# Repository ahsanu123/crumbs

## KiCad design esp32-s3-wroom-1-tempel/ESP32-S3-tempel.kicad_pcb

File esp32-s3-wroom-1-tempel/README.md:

# Logs 

- 16 Februari 2026, make a prototype board, but not sure why its not able detected in pc. need to recheck schematic and re make the prototype board.

# ESP32 S3 Tempel

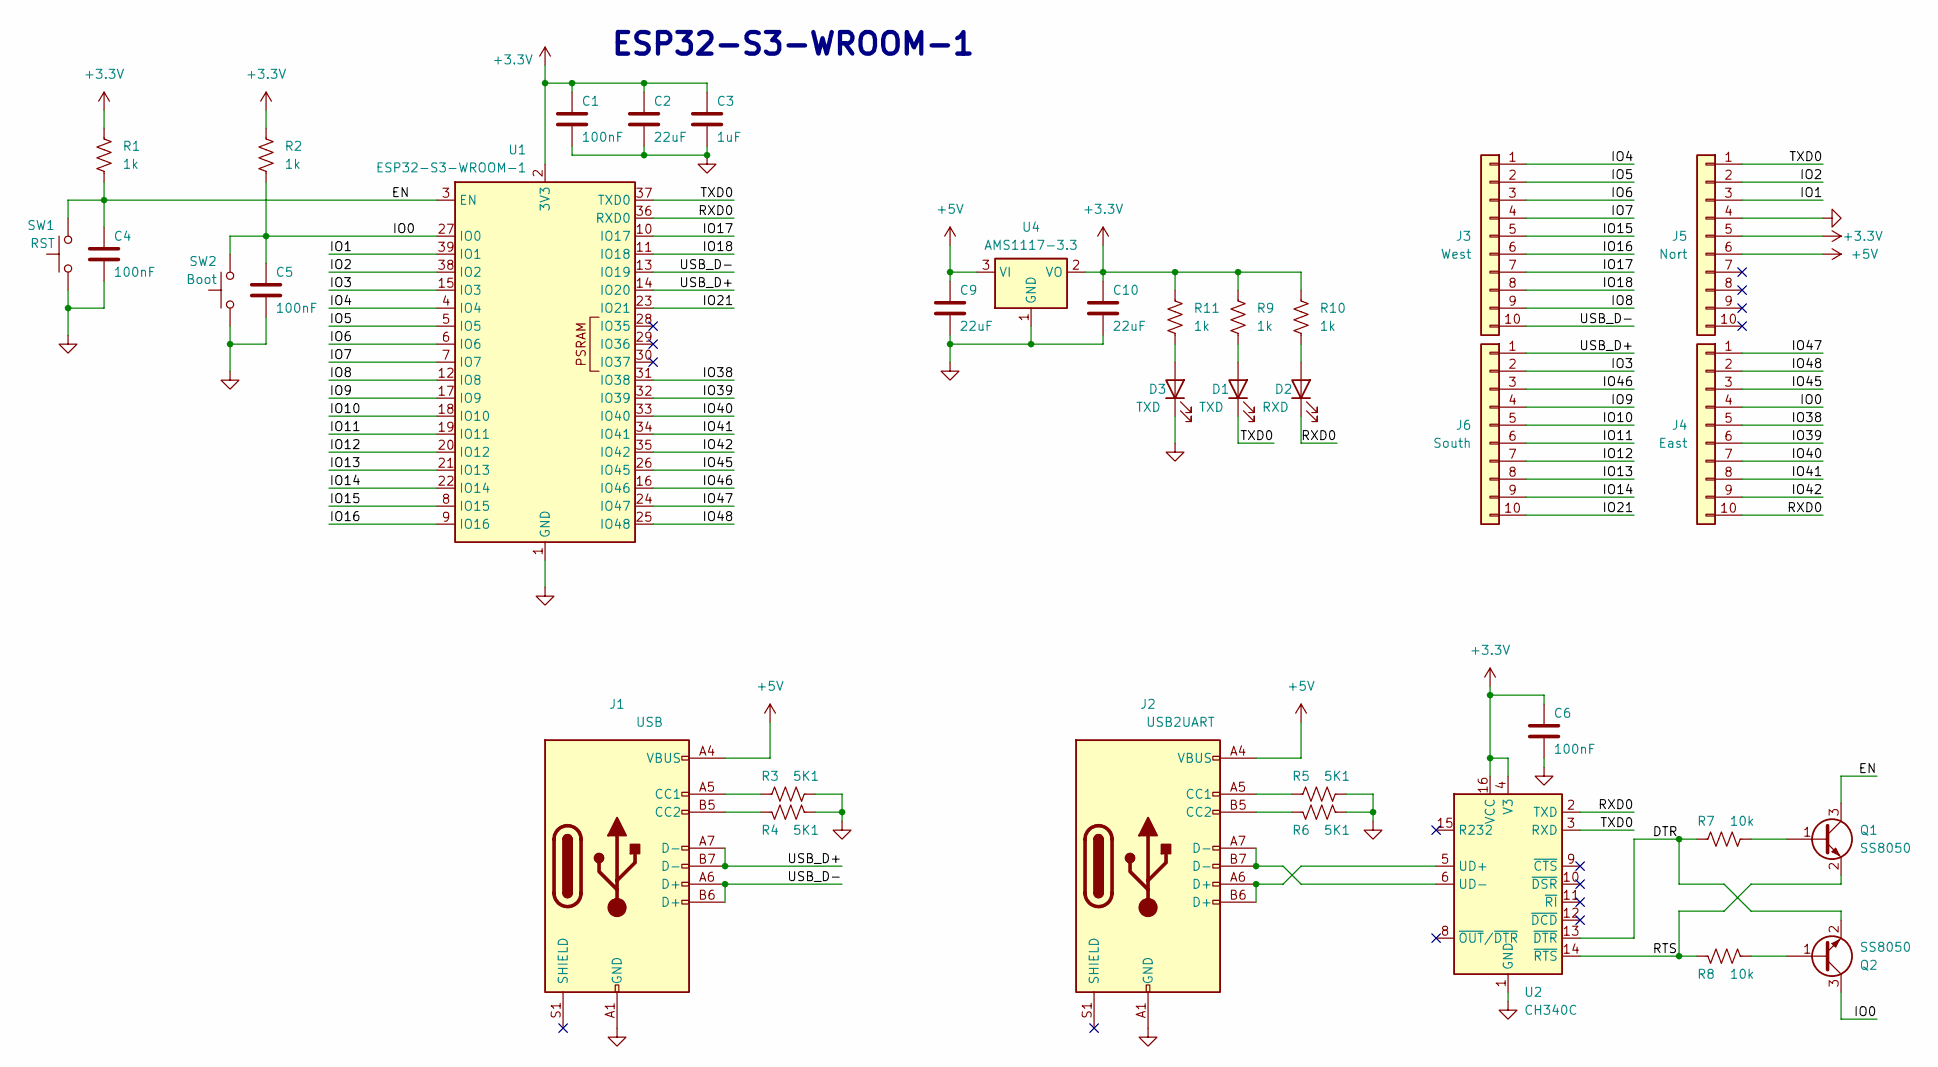
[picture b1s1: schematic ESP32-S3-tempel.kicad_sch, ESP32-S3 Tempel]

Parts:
C1, C4, C5, C6: 100nF; C_0805_2012Metric_Pad1.18x1.45mm_HandSolder
C2, C9, C10: 22uF; C_0805_2012Metric_Pad1.18x1.45mm_HandSolder
C3: 1uF; C_0805_2012Metric_Pad1.18x1.45mm_HandSolder
D1, D3: TXD; LED_1206_3216Metric_Pad1.42x1.75mm_HandSolder
D2: RXD; LED_1206_3216Metric_Pad1.42x1.75mm_HandSolder
J1: USB; USB_C_Receptacle_GCT_USB4110
J2: USB2UART; USB_C_Receptacle_GCT_USB4110
J3: West; PinHeader_1x10_P2.54mm_Vertical
J4: East; PinHeader_1x10_P2.54mm_Vertical
J5: Nort; PinHeader_1x10_P2.54mm_Vertical
J6: South; PinHeader_1x10_P2.54mm_Vertical
Q1, Q2: SS8050; SOT-23_Handsoldering
R1, R2, R9, R10, R11: 1k; R_0805_2012Metric_Pad1.20x1.40mm_HandSolder
R3, R4, R5, R6: 5K1; R_0805_2012Metric_Pad1.20x1.40mm_HandSolder
R7, R8: 10k; R_0805_2012Metric_Pad1.20x1.40mm_HandSolder
SW1: RST; SW_Push_1P1T_NO_6x6mm_H9.5mm
SW2: Boot; SW_Push_1P1T_NO_6x6mm_H9.5mm
U1: ESP32-S3-WROOM-1
U2: CH340C; SOIC-16_3.9x9.9mm_P1.27mm
U4: AMS1117-3.3; SOT-223-3_TabPin2

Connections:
+3.3V: C1.1, C2.1, C3.1, C6.1, C10.1, J5.5, R1.1, R2.1, R9.1, R10.1, R11.1, U1.2 (3V3), U2.4 (V3), U2.16 (VCC), U4.2 (VO)
+5V: C9.1, J1.A4 (VBUS), J1.A9 (VBUS), J1.B4 (VBUS), J1.B9 (VBUS), J2.A4 (VBUS), J2.A9 (VBUS), J2.B4 (VBUS), J2.B9 (VBUS), J5.6, U4.3 (VI)
/DTR: Q2.2 (E), R7.2, U2.13 (~DTR)
/EN: C4.1, Q1.3 (C), R1.2, SW1.2, U1.3 (EN)
/IO0: C5.1, J4.4, Q2.3 (C), R2.2, SW2.2, U1.27 (IO0)
/IO1: J5.3, U1.39 (IO1)
/IO2: J5.2, U1.38 (IO2)
/IO3: J6.2, U1.15 (IO3)
/IO4: J3.1, U1.4 (IO4)
/IO5: J3.2, U1.5 (IO5)
/IO6: J3.3, U1.6 (IO6)
/IO7: J3.4, U1.7 (IO7)
/IO8: J3.9, U1.12 (IO8)
/IO9: J6.4, U1.17 (IO9)
/IO10: J6.5, U1.18 (IO10)
/IO11: J6.6, U1.19 (IO11)
/IO12: J6.7, U1.20 (IO12)
/IO13: J6.8, U1.21 (IO13)
/IO14: J6.9, U1.22 (IO14)
/IO15: J3.5, U1.8 (IO15)
/IO16: J3.6, U1.9 (IO16)
/IO17: J3.7, U1.10 (IO17)
/IO18: J3.8, U1.11 (IO18)
/IO21: J6.10, U1.23 (IO21)
/IO38: J4.5, U1.31 (IO38)
/IO39: J4.6, U1.32 (IO39)
/IO40: J4.7, U1.33 (IO40)
/IO41: J4.8, U1.34 (IO41)
/IO42: J4.9, U1.35 (IO42)
/IO45: J4.3, U1.26 (IO45)
/IO46: J6.3, U1.16 (IO46)
/IO47: J4.1, U1.24 (IO47)
/IO48: J4.2, U1.25 (IO48)
/RTS: Q1.2 (E), R8.2, U2.14 (~RTS)
/RXD0: D2.1 (K), J4.10, U1.36 (RXD0), U2.2 (TXD)
/TXD0: D1.1 (K), J5.1, U1.37 (TXD0), U2.3 (RXD)
/USB_D+: J1.A7 (D-), J1.B7 (D-), J6.1, U1.14 (IO20)
/USB_D-: J1.A6 (D+), J1.B6 (D+), J3.10, U1.13 (IO19)
GND: C1.2, C2.2, C3.2, C4.2, C5.2, C6.2, C9.2, C10.2, D3.1 (K), J1.A1 (GND), J1.A12 (GND), J1.B1 (GND), J1.B12 (GND), J2.A1 (GND), J2.A12 (GND), J2.B1 (GND), J2.B12 (GND), J5.4, R3.1, R4.1, R5.1, R6.1, SW1.1, SW2.1, U1.1 (GND), U1.40 (GND), U1.41 (GND), U2.1 (GND), U4.1 (GND)
unnamed: D1.2 (A), R9.2
unnamed: D2.2 (A), R10.2
unnamed: D3.2 (A), R11.2
unnamed: J1.A5 (CC1), R3.2
unnamed: J1.B5 (CC2), R4.2
unnamed: J2.A5 (CC1), R5.2
unnamed: J2.B5 (CC2), R6.2
unnamed: Q1.1 (B), R7.1
unnamed: Q2.1 (B), R8.1
unnamed: J2.A6 (D+), J2.B6 (D+), U2.5 (UD+)
unnamed: J2.A7 (D-), J2.B7 (D-), U2.6 (UD-)

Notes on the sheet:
ESP32-S3-WROOM-1

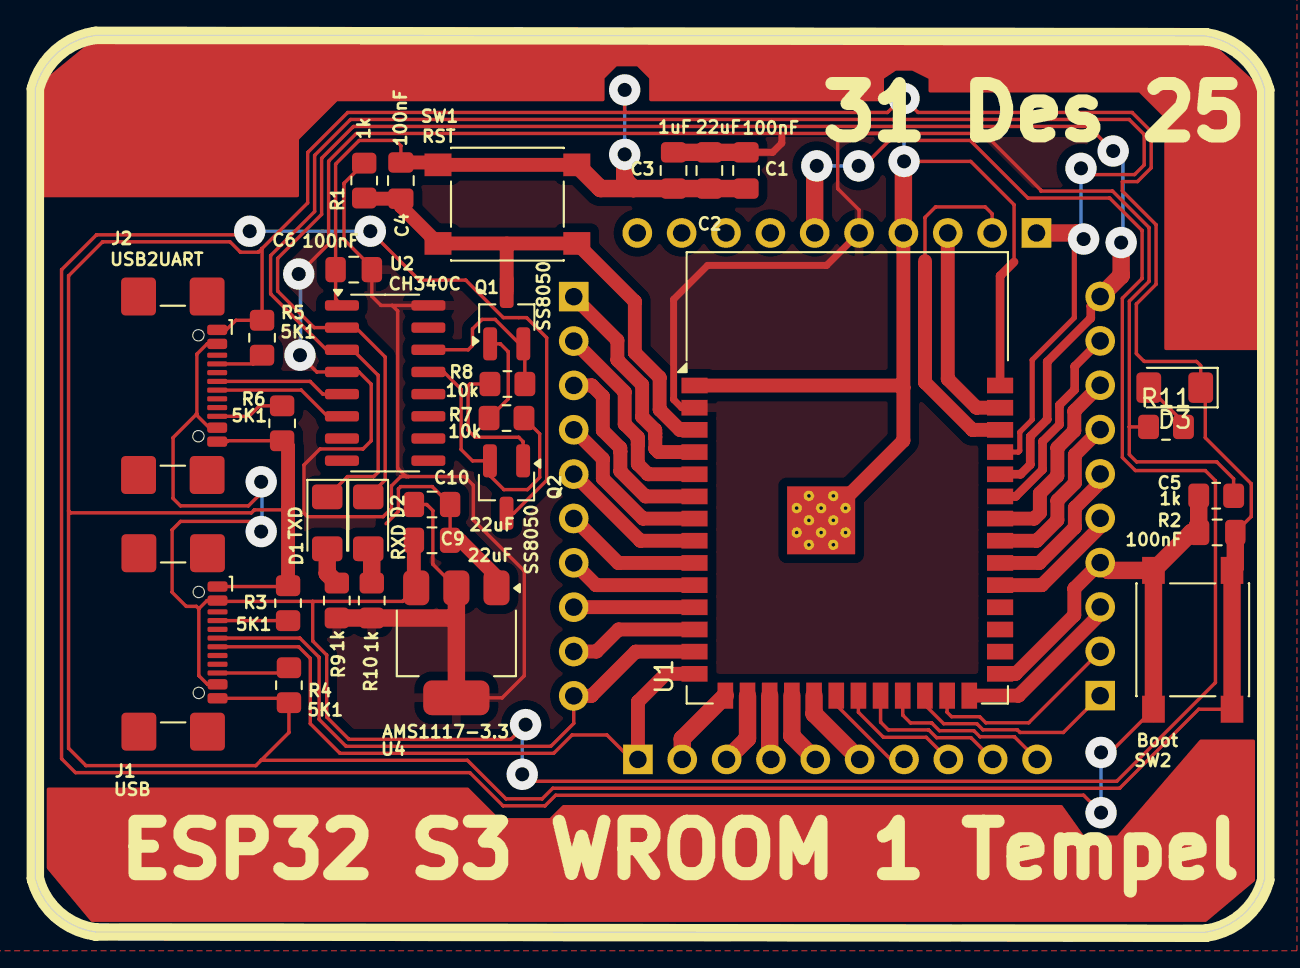
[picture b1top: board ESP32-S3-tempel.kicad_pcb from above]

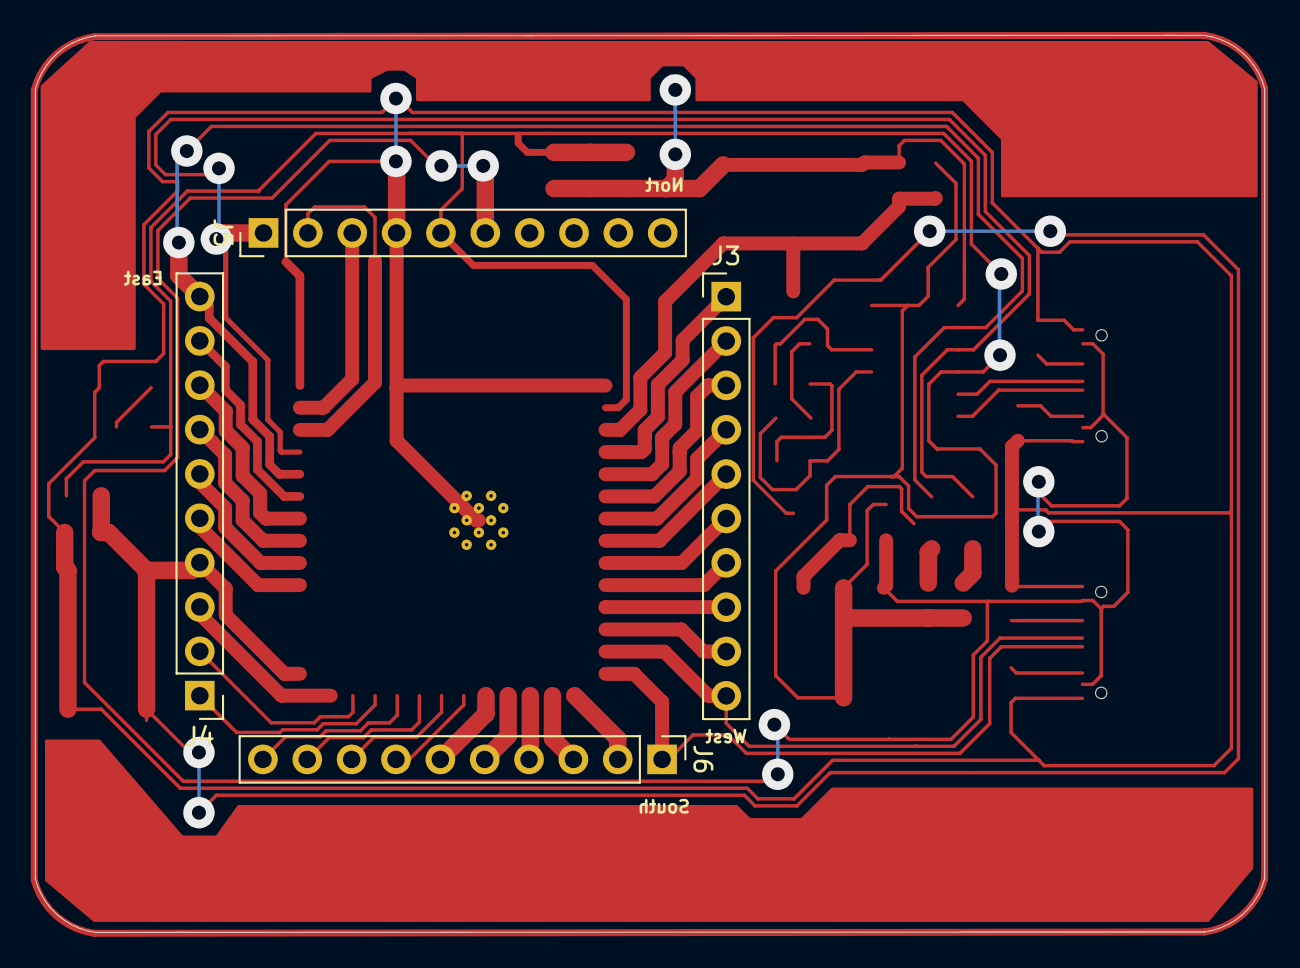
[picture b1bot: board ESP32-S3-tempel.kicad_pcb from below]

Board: 2 copper layers, 70.4 x 51.4 mm, 35 parts (4 on the bottom side), 50 nets.

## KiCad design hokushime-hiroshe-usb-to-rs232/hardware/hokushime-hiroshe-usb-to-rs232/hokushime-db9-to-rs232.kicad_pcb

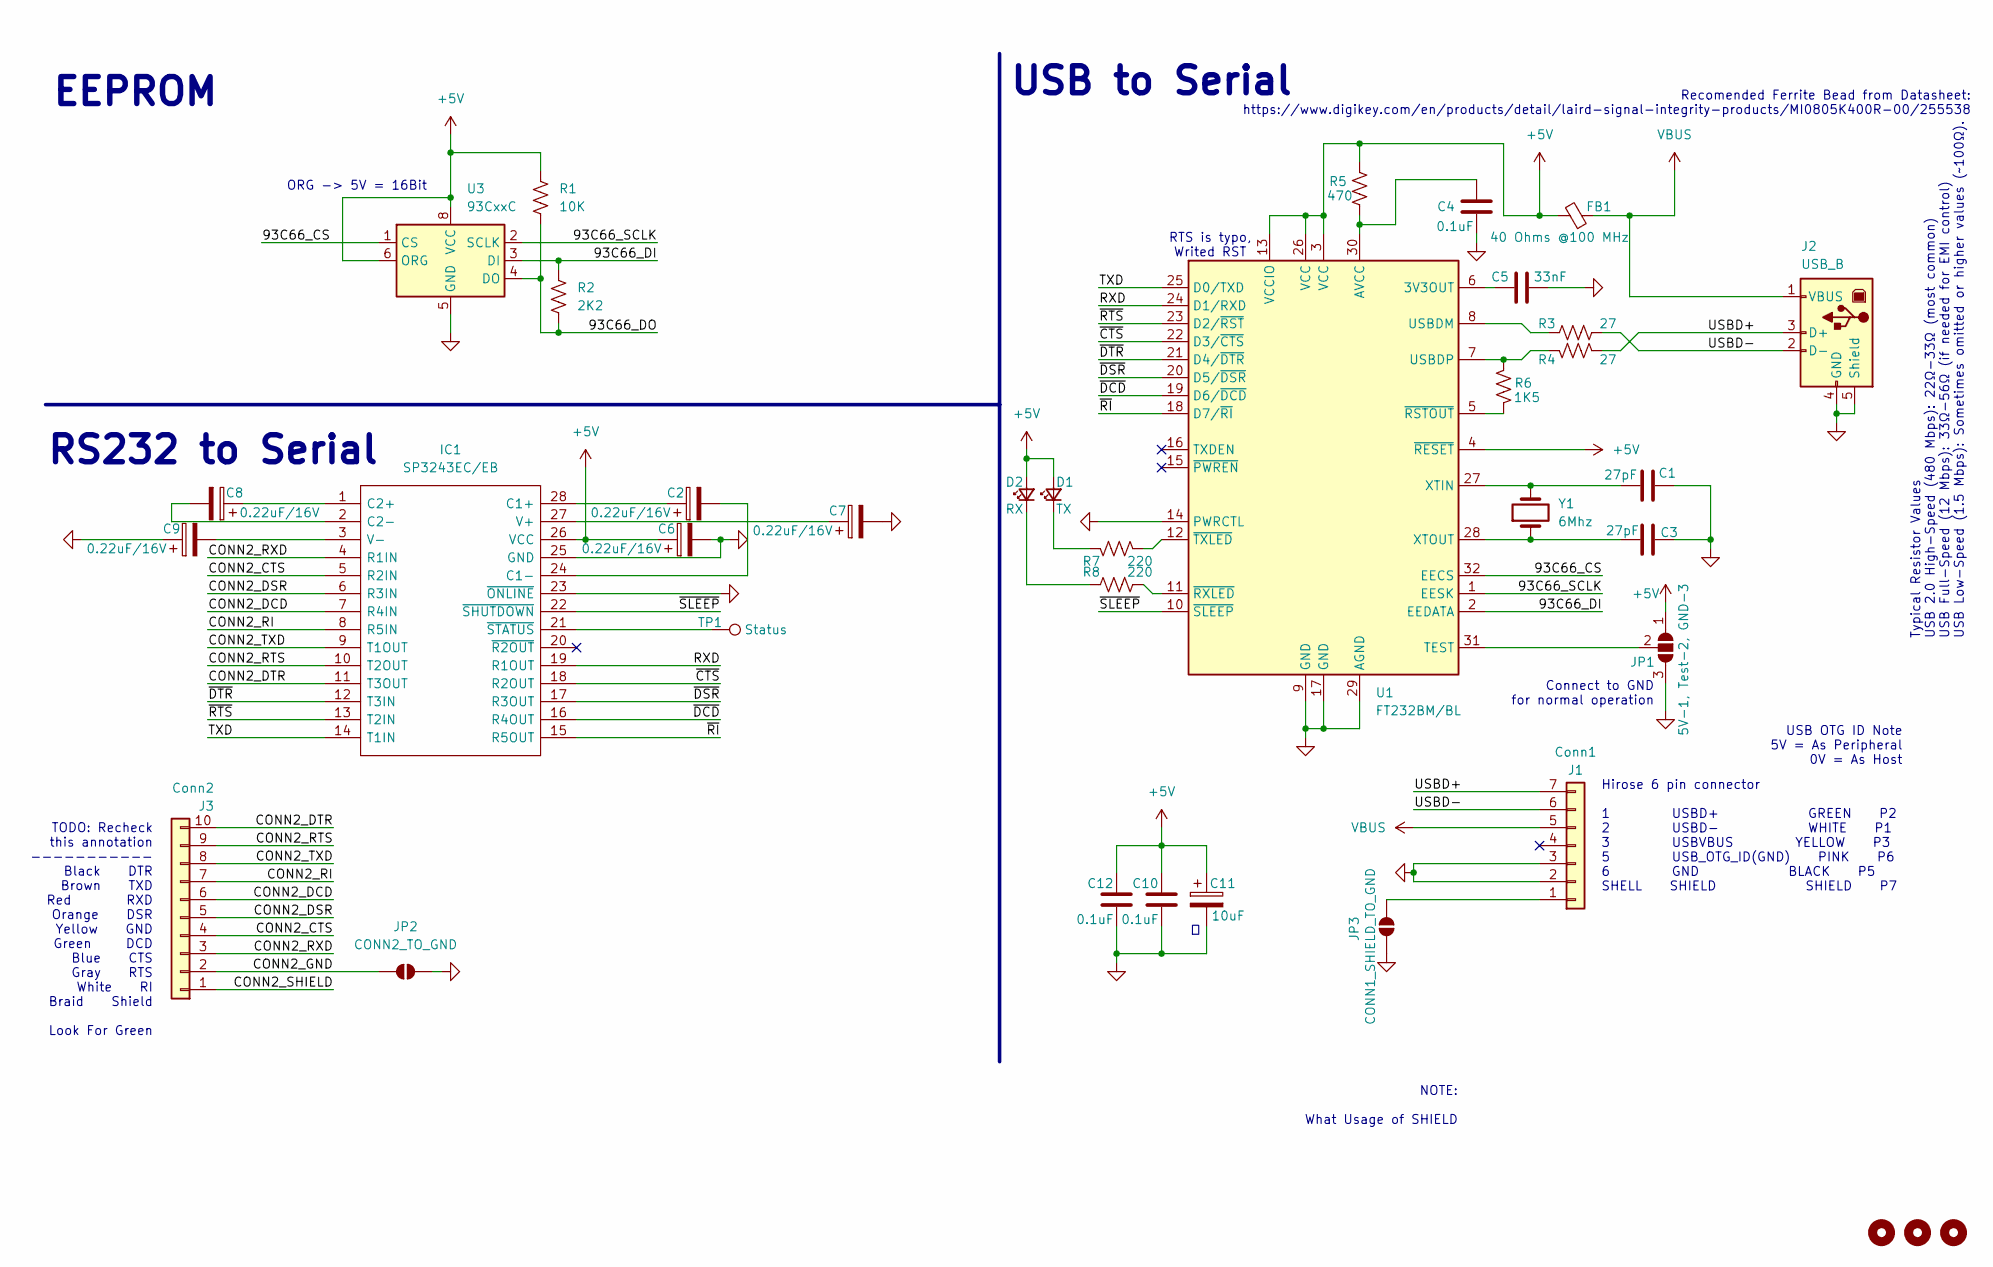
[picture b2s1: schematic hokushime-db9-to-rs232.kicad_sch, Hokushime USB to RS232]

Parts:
C1, C3: 27pF; C_0603_1608Metric_Pad1.08x0.95mm_HandSolder
C2, C6, C7, C8, C9: 0.22uF/16V; C_0603_1608Metric_Pad1.08x0.95mm_HandSolder
C4, C10, C12: 0.1uF; C_0603_1608Metric_Pad1.08x0.95mm_HandSolder
C5: 33nF; C_0603_1608Metric_Pad1.08x0.95mm_HandSolder
C11: 10uF; C_0603_1608Metric_Pad1.08x0.95mm_HandSolder
D1: TX; LED_0805_2012Metric_Pad1.15x1.40mm_HandSolder
D2: RX; LED_0805_2012Metric_Pad1.15x1.40mm_HandSolder
FB1: 40 Ohms @100 MHz; L_0603_1608Metric_Pad1.05x0.95mm_HandSolder
H1, H2, H4: MountingHole; MountingHole_3mm
IC1: SP3243EC/EB; SSOP-28_5.3x10.2mm_P0.65mm; Manufacturer_Part_Number SP3243ECA-L
J1: Conn1; PinHeader_1x07_P2.54mm_Horizontal
J2: USB_B; USB_B_Lumberg_2411_02_Horizontal
J3: Conn2; PinHeader_1x10_P2.54mm_Horizontal
JP1: 5V-1, Test-2, GND-3; SolderJumper-3_P2.0mm_Open_TrianglePad1.0x1.5mm_NumberLabels
JP2: CONN2_TO_GND; SolderJumper-2_P1.3mm_Open_RoundedPad1.0x1.5mm
JP3: CONN1_SHIELD_TO_GND; SolderJumper-2_P1.3mm_Open_RoundedPad1.0x1.5mm
R1: 10K; R_0805_2012Metric_Pad1.20x1.40mm_HandSolder
R2: 2K2; R_0805_2012Metric_Pad1.20x1.40mm_HandSolder
R3, R4: 27; R_0805_2012Metric_Pad1.20x1.40mm_HandSolder
R5: 470; R_0805_2012Metric_Pad1.20x1.40mm_HandSolder
R6: 1K5; R_0805_2012Metric_Pad1.20x1.40mm_HandSolder
R7, R8: 220; R_0805_2012Metric_Pad1.20x1.40mm_HandSolder
TP1: Status; TestPoint_Pad_D1.0mm
U1: FT232BM/BL; LQFP-32_7x7mm_P0.8mm
U3: 93CxxC; SOIC-8_3.9x4.9mm_P1.27mm
Y1: 6Mhz; Crystal_HC49-U_Vertical

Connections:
+5V: C6.1, C10.2, C11.1, C12.2, D1.2 (A), D2.2 (A), FB1.2, IC1.26 (VCC), JP1.1 (A), R1.1, R5.2, U1.3 (VCC), U1.4 (~RESET), U1.13 (VCCIO), U1.26 (VCC), U3.6 (ORG), U3.8 (VCC)
/93C66_CS: U1.32 (EECS), U3.1 (CS)
/93C66_DI: R2.1, U1.2 (EEDATA), U3.3 (DI)
/93C66_DO: R1.2, R2.2, U3.4 (DO)
/93C66_SCLK: U1.1 (EESK), U3.2 (SCLK)
/CONN2_CTS: IC1.5 (R2IN), J3.4
/CONN2_DCD: IC1.7 (R4IN), J3.6
/CONN2_DSR: IC1.6 (R3IN), J3.5
/CONN2_DTR: IC1.11 (T3OUT), J3.10
/CONN2_GND: J3.2, JP2.1 (A)
/CONN2_RI: IC1.8 (R5IN), J3.7
/CONN2_RTS: IC1.10 (T2OUT), J3.9
/CONN2_RXD: IC1.4 (R1IN), J3.3
/CONN2_SHIELD: J3.1
/CONN2_TXD: IC1.9 (T1OUT), J3.8
/RXD: IC1.19 (R1OUT), U1.24 (D1/RXD)
/TXD: IC1.14 (T1IN), U1.25 (D0/TXD)
/USBD+: J1.7, J2.3 (D+), R4.2
/USBD-: J1.6, J2.2 (D-), R3.2
/~CTS: IC1.18 (R2OUT), U1.22 (D3/~CTS)
/~DCD: IC1.16 (R4OUT), U1.19 (D6/~DCD)
/~DSR: IC1.17 (R3OUT), U1.20 (D5/~DSR)
/~DTR: IC1.12 (T3IN), U1.21 (D4/~DTR)
/~RI: IC1.15 (R5OUT), U1.18 (D7/~RI)
/~RTS: IC1.13 (T2IN), U1.23 (D2/~RST)
/~SLEEP: IC1.22 (~SHUTDOWN), U1.10 (~SLEEP)
GND: C1.2, C3.2, C4.1, C5.1, C6.2, C7.2, C9.1, C10.1, C11.2, C12.1, IC1.23 (~ONLINE), IC1.25 (GND), J1.2, J1.3, J2.4 (GND), J2.5 (Shield), JP1.3 (B), JP2.2 (B), JP3.1 (A), U1.9 (GND), U1.14 (PWRCTL), U1.17 (GND), U1.29 (AGND), U3.5 (GND)
unnamed: D1.1 (K), R7.1
unnamed: D2.1 (K), R8.1
unnamed: C2.1, IC1.28 (C1+)
unnamed: C2.2, IC1.24 (C1-)
unnamed: C8.1, IC1.1 (C2+)
unnamed: C8.2, IC1.2 (C2-)
unnamed: C7.1, IC1.27 (V+)
unnamed: C9.2, IC1.3 (V-)
unnamed: IC1.21 (~STATUS), TP1.1
unnamed: J1.1, JP3.2 (B)
unnamed: JP1.2 (C), U1.31 (TEST)
unnamed: C5.2, U1.6 (3V3OUT)
unnamed: C4.2, R5.1, U1.30 (AVCC)
unnamed: R3.1, U1.8 (USBDM)
unnamed: R4.1, R6.2, U1.7 (USBDP)
unnamed: C1.1, U1.27 (XTIN), Y1.2
unnamed: C3.1, U1.28 (XTOUT), Y1.1
unnamed: R6.1, U1.5 (~RSTOUT)
unnamed: R8.2, U1.11 (~RXLED)
unnamed: R7.2, U1.12 (~TXLED)
VBUS: FB1.1, J1.5, J2.1 (VBUS)

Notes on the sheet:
TODO: Recheck this annotation ----------- Black DTR Brown TXD Red RXD Orange DSR Yellow GND Green DCD Blue CTS Gray RTS White RI Braid Shield Look For Green
ORG -> 5V = 16Bit
Recomended Ferrite Bead from Datasheet: https://www.digikey.com/en/products/detail/laird-signal-integrity-products/MI0805K400R-00/255538
RS232 to Serial
USB OTG ID Note 5V = As Peripheral 0V = As Host
RTS is typo, Writed RST
Typical Resistor Values USB 2.0 High-Speed (480 Mbps): 22Ω-33Ω (most common) USB Full-Speed (12 Mbps): 33Ω-56Ω (if needed for EMI control) USB Low-Speed (1.5 Mbps): Sometimes omitted or higher values (~100Ω).
Connect to GND for normal operation
EEPROM
Hirose 6 pin connector 1 USBD+ GREEN P2 2 USBD- WHITE P1 3 USBVBUS YELLOW P3 5 USB_OTG_ID(GND) PINK P6 6 GND BLACK P5 SHELL SHIELD SHIELD P7
NOTE: What Usage of SHIELD
USB to Serial

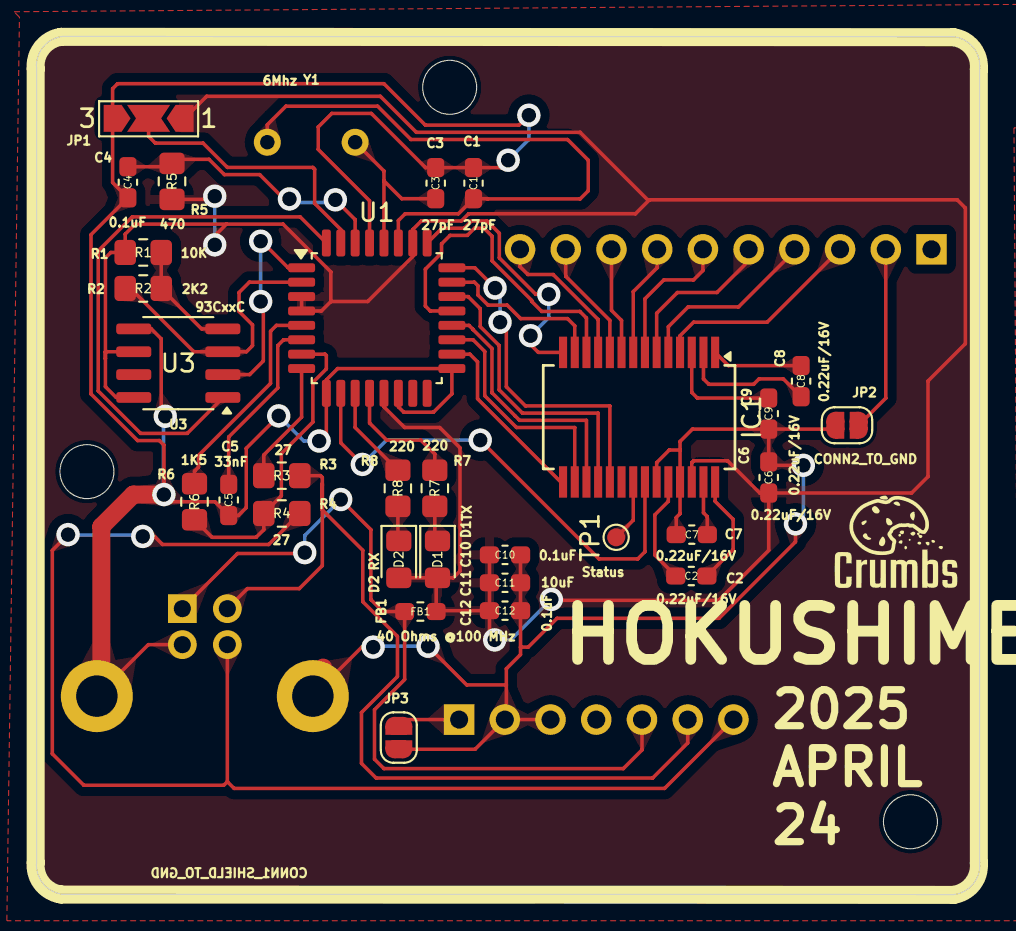
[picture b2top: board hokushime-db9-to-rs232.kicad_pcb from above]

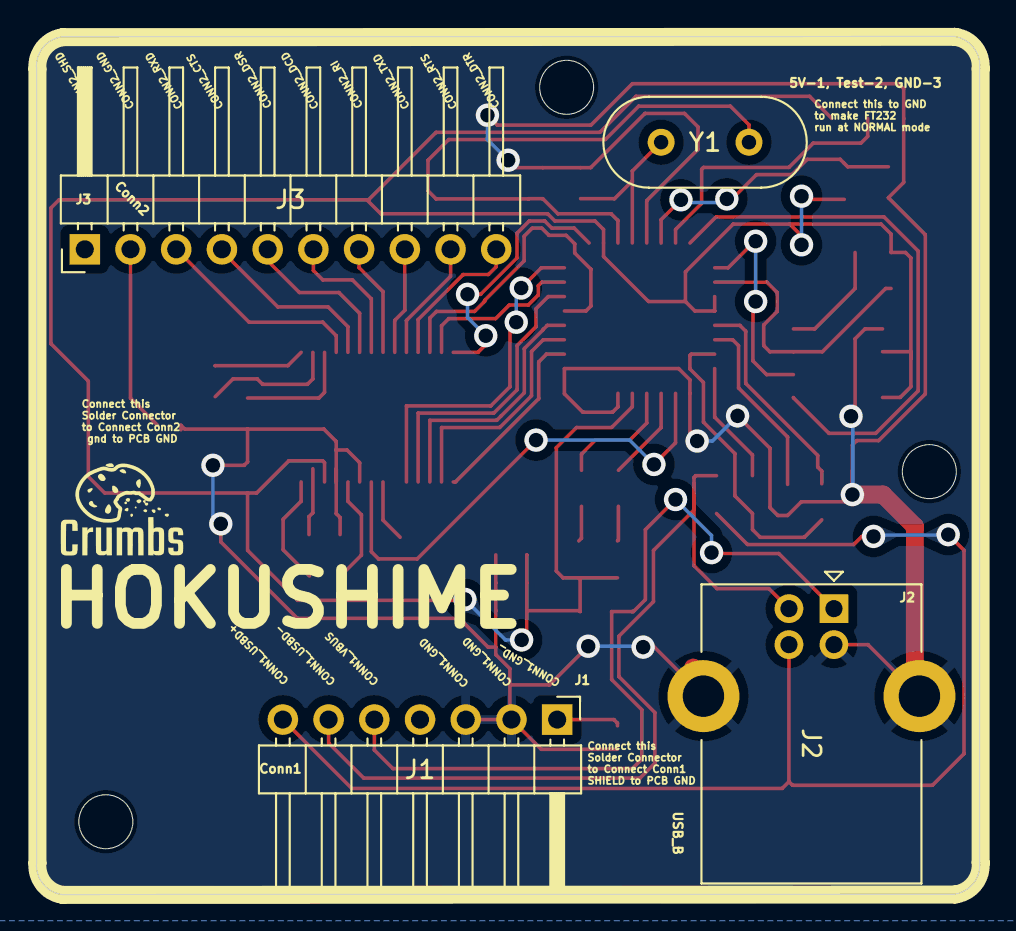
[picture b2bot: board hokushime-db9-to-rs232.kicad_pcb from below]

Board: 2 copper layers, 52.4 x 47.7 mm, 39 parts (5 on the bottom side), 47 nets.

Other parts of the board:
G1, G1#2: LOGO; Crumbs-Logo_Footprint_13x13

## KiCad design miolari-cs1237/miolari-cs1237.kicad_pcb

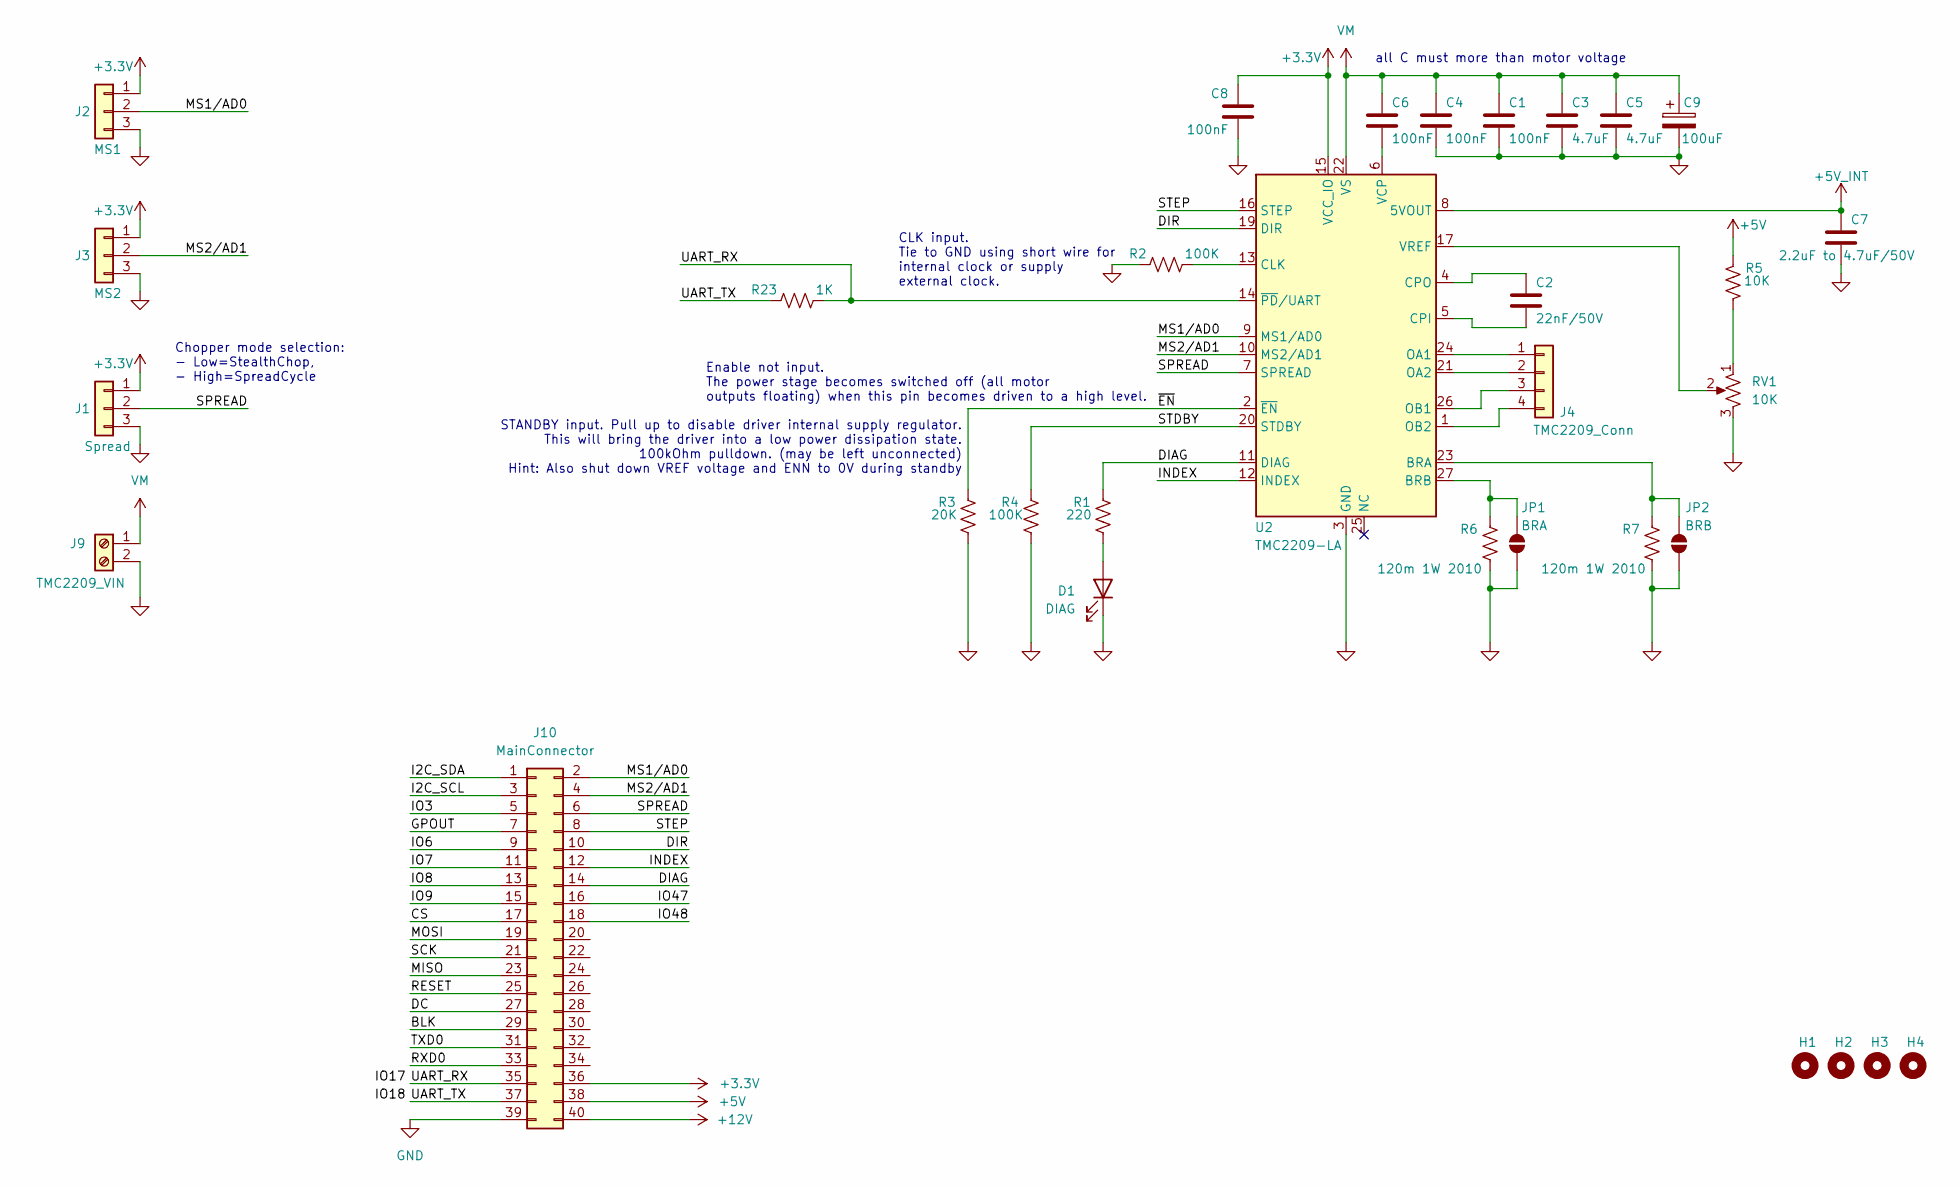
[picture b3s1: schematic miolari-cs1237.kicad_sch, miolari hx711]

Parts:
C1, C4, C6, C8: 100nF; C_0805_2012Metric_Pad1.18x1.45mm_HandSolder
C2: 22nF/50V; C_0805_2012Metric_Pad1.18x1.45mm_HandSolder
C3, C5: 4.7uF; C_0805_2012Metric_Pad1.18x1.45mm_HandSolder
C7: 2.2uF to 4.7uF/50V; C_0805_2012Metric_Pad1.18x1.45mm_HandSolder
C9: 100uF; CP_Radial_D8.0mm_P3.50mm
D1: DIAG; LED_0805_2012Metric_Pad1.15x1.40mm_HandSolder
H1, H2, H3, H4: MountingHole; MountingHole_2mm
J1: Spread; PinHeader_1x03_P2.54mm_Vertical
J2: MS1; PinHeader_1x03_P2.54mm_Vertical
J3: MS2; PinHeader_1x03_P2.54mm_Vertical
J4: TMC2209_Conn; Molex_Nano-Fit_105313-xx04_1x04_P2.50mm_Horizontal
J9: TMC2209_VIN; TerminalBlock_Phoenix_PT-1,5-2-5.0-H_1x02_P5.00mm_Horizontal
J10: MainConnector; IDC-Header_2x20_P2.54mm_Vertical
JP1: BRA; SolderJumper-2_P1.3mm_Open_RoundedPad1.0x1.5mm
JP2: BRB; SolderJumper-2_P1.3mm_Open_RoundedPad1.0x1.5mm
R1: 220; R_0805_2012Metric_Pad1.20x1.40mm_HandSolder
R2, R4: 100K; R_0805_2012Metric_Pad1.20x1.40mm_HandSolder
R3: 20K; R_0805_2012Metric_Pad1.20x1.40mm_HandSolder
R5: 10K; R_0805_2012Metric_Pad1.20x1.40mm_HandSolder
R6, R7: 120m 1W 2010; R_2010_5025Metric
R23: 1K; R_0805_2012Metric_Pad1.20x1.40mm_HandSolder
RV1: 10K; Potentiometer_Bourns_3269W_Vertical
U2: TMC2209-LA; VQFN-28-1EP_5x5mm_P0.5mm_EP3.7x3.7mm

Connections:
+3.3V: C8.1, J1.1, J2.1, J3.1, J10.36, U2.15 (VCC_IO)
+5V: J10.38, R5.1
+5V_INT: C7.1, U2.8 (5VOUT)
+12V: J10.40
/BLK: J10.29
/CS: J10.17
/DC: J10.27
/DIAG: J10.14, R1.1, U2.11 (DIAG)
/DIR: J10.10, U2.19 (DIR)
/GPOUT: J10.7
/I2C_SCL: J10.3
/I2C_SDA: J10.1
/INDEX: J10.12, U2.12 (INDEX)
/IO3: J10.5
/IO6: J10.9
/IO7: J10.11
/IO8: J10.13
/IO9: J10.15
/IO47: J10.16
/IO48: J10.18
/MISO: J10.23
/MOSI: J10.19
/MS1/AD0: J2.2, J10.2, U2.9 (MS1/AD0)
/MS2/AD1: J3.2, J10.4, U2.10 (MS2/AD1)
/RESET: J10.25
/RXD0: J10.33
/SCK: J10.21
/SPREAD: J1.2, J10.6, U2.7 (SPREAD)
/STDBY: R4.1, U2.20 (STDBY)
/STEP: J10.8, U2.16 (STEP)
/TXD0: J10.31
/UART_RX: J10.35, R23.1, U2.14 (~PD/UART)
/UART_TX: J10.37, R23.2
/~EN: R3.1, U2.2 (~EN)
GND: C1.2, C3.2, C4.2, C5.2, C7.2, C8.2, C9.2, D1.1 (K), J1.3, J2.3, J3.3, J9.2, J10.39, JP1.1 (A), JP2.1 (A), R2.2, R3.2, R4.2, R6.2, R7.2, RV1.3, U2.3 (GND), U2.18 (GND), U2.29 (GND)
unnamed: D1.2 (A), R1.2
unnamed: J4.1, U2.24 (OA1)
unnamed: J4.2, U2.21 (OA2)
unnamed: J4.3, U2.26 (OB1)
unnamed: J4.4, U2.1 (OB2)
unnamed: JP1.2 (B), R6.1, U2.27 (BRB)
unnamed: JP2.2 (B), R7.1, U2.23 (BRA)
unnamed: R5.2, RV1.1
unnamed: R2.1, U2.13 (CLK)
unnamed: C2.2, U2.5 (CPI)
unnamed: C2.1, U2.4 (CPO)
unnamed: C6.2, U2.6 (VCP)
unnamed: RV1.2, U2.17 (VREF)
VM: C1.1, C3.1, C4.1, C5.1, C6.1, C9.1, J9.1, U2.22 (VS), U2.28 (VS)

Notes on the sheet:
Chopper mode selection: - Low=StealthChop, - High=SpreadCycle
all C must more than motor voltage
Enable not input. The power stage becomes switched off (all motor outputs floating) when this pin becomes driven to a high level.
STANDBY input. Pull up to disable driver internal supply regulator. This will bring the driver into a low power dissipation state. 100kOhm pulldown. (may be left unconnected) Hint: Also shut down VREF voltage and ENN to 0V during standby
CLK input. Tie to GND using short wire for internal clock or supply external clock.

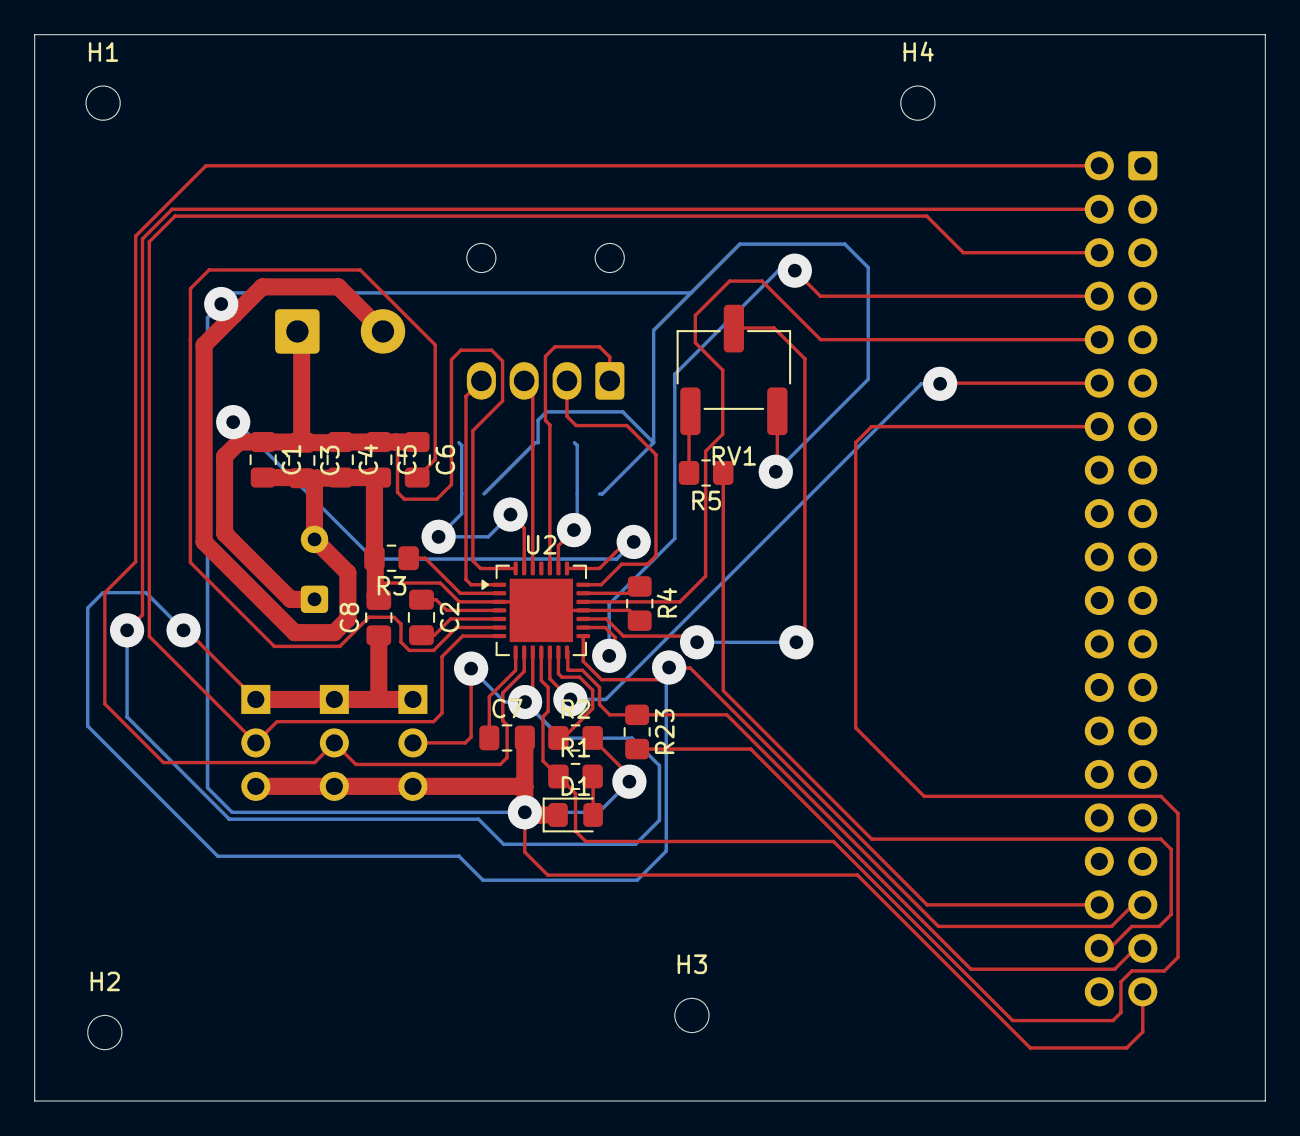
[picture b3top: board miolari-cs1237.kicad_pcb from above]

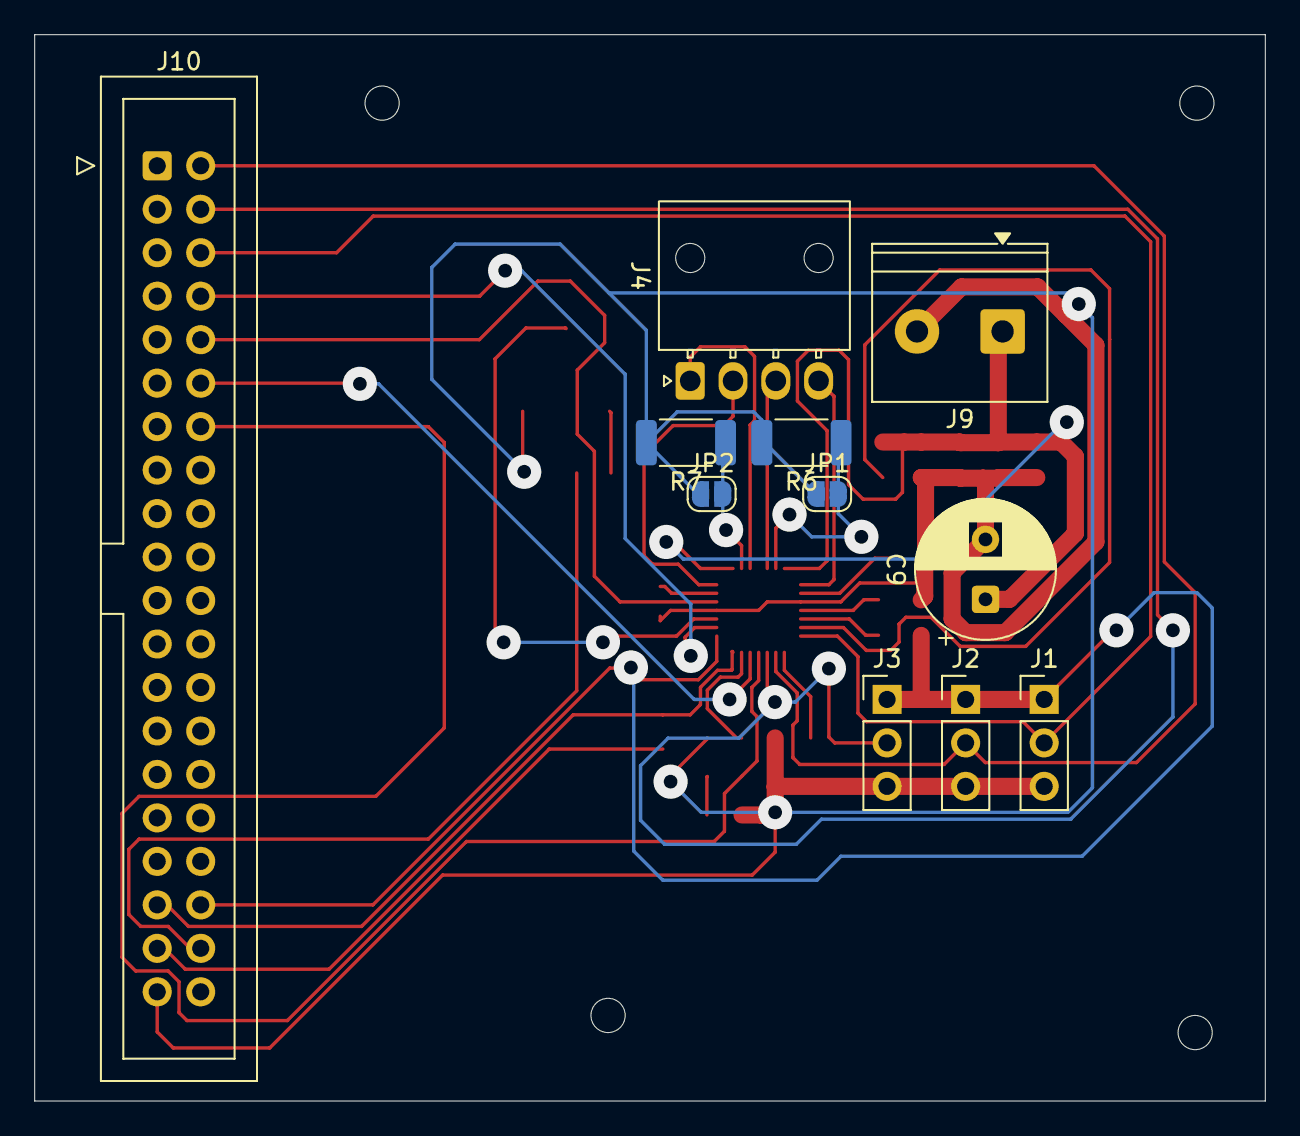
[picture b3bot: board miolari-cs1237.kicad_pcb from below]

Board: 2 copper layers, 71.9 x 62.3 mm, 32 parts (11 on the bottom side), 29 nets.
